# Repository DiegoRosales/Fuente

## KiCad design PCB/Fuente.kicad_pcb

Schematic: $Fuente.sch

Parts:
C1: 0.33uF
C2, C3, C5, C6: 0.1uF
C4, C7: 470uF
D1, D2, D3, D4, D9, D10, D11, D12, D17, D18, D19, D20, D25, D26, D27, D28: LED
D5, D6, D7, D8, D13, D14, D15, D16, D21, D22, D23, D24, D29, D30, D31, D32, D33: DIODE
FB1: FILTER
JP1: JUMPER
JP2: JUMPER
JP3: JUMPER3
MCU1: PRO_MINI_2
P1, P2, P3, P4, P5, P6, P7, P8, P9, P10, P11, P12, P13, P14, P15, P16, P17, P18: CONN_2
P19, P20: CONN_4
Q1, Q2, Q3, Q4, Q5, Q6, Q7, Q8, Q9, Q10, Q11, Q12, Q13, Q14, Q15, Q16: MOSFET_N
R1, R2, R3, R4, R5, R6, R7, R8, R9, R10, R11, R12, R13, R14, R15, R16, R17, R18, R19: 1k
SD1: MICROSD_MODULE
SW1, SW2, SW3, SW4, SW5, SW6, SW7, SW8, SW9, SW10, SW11, SW12, SW13, SW14, SW15, SW16: PUSHBUTTON
U1: 7805
U2, U3: 74HC595
U4: BTM_2

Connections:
1: SW1.2, U2.15 (QA)
2: SW5.2, U2.1 (QB)
3: SW9.2, U2.2 (QC)
4: SW13.2, U2.3 (QD)
5: SW2.2, U2.4 (QE)
6: SW6.2, U2.5 (QF)
7: SW10.2, U2.6 (QG)
8: SW14.2, U2.7 (QH)
9: SW3.2, U3.15 (QA)
10: SW7.2, U3.1 (QB)
11: SW11.2, U3.2 (QC)
12: SW15.2, U3.3 (QD)
13: SW4.2, U3.4 (QE)
14: SW8.2, U3.5 (QF)
15: SW12.2, U3.6 (QG)
16: SW16.2, U3.7 (QH)
+5V: C2.1, C3.1, C4.1, FB1.1, JP1.1, MCU1.25, SD1.3 (VCC), SW1.3, SW1.4, SW2.3, SW2.4, SW3.3, SW3.4, SW4.3, SW4.4, SW5.3, SW5.4, SW6.3, SW6.4, SW7.3, SW7.4, SW8.3, SW8.4, SW9.3, SW9.4, SW10.3, SW10.4, SW11.3, SW11.4, SW12.3, SW12.4, SW13.3, SW13.4, SW14.3, SW14.4, SW15.3, SW15.4, SW16.3, SW16.4, U2.10 (SRCLR), U2.16 (VCC), U3.10 (SRCLR), U3.16 (VCC)
+12P: C1.1, D33.2 (K), P18.2 (PM), U1.VI, U1.Vi
+12V: C5.1, C7.1, D5.2 (K), D6.2 (K), D7.2 (K), D8.2 (K), D13.2 (K), D14.2 (K), D15.2 (K), D16.2 (K), D21.2 (K), D22.2 (K), D23.2 (K), D24.2 (K), D29.2 (K), D30.2 (K), D31.2 (K), D32.2 (K), P1.1, P2.1, P3.1, P4.1, P5.1, P6.1, P7.1, P8.1, P9.1, P10.1, P11.1, P12.1, P13.1, P14.1, P15.1, P16.1, P17.2 (PM)
/M_S: JP2.1, MCU1.8
A0 (RX): MCU1.21, U4.3 (TX)
A1 (TX): MCU1.22, R18.2, R19.1
GND: C1.2, C2.2, C3.2, C4.2, C5.2, C6.2, C7.2, D1.2 (K), D2.2 (K), D3.2 (K), D4.2 (K), D9.2 (K), D10.2 (K), D11.2 (K), D12.2 (K), D17.2 (K), D18.2 (K), D19.2 (K), D20.2 (K), D25.2 (K), D26.2 (K), D27.2 (K), D28.2 (K), JP2.2, MCU1.4, MCU1.27, P17.1, P18.1, Q1.S, Q2.S, Q3.S, Q4.S, Q5.S, Q6.S, Q7.S, Q8.S, Q9.S, Q10.S, Q11.S, Q12.S, Q13.S, Q14.S, Q15.S, Q16.S, R17.1, SD1.2 (GND), U1.GND, U2.8 (GND), U3.8 (GND), U4.4 (GND)
unnamed: Q13.G, R13.2, SW13.1
unnamed: D25.1 (A), R13.1
unnamed: Q2.G, R2.2, SW2.1
unnamed: D17.1 (A), R9.1
unnamed: D9.1 (A), R5.1
unnamed: Q5.G, R5.2, SW5.1
unnamed: Q9.G, R9.2, SW9.1
unnamed: D18.1 (A), R10.1
unnamed: Q10.G, R10.2, SW10.1
unnamed: D26.1 (A), R14.1
unnamed: Q14.G, R14.2, SW14.1
unnamed: Q6.G, R6.2, SW6.1
unnamed: D2.1 (A), R2.1
unnamed: D10.1 (A), R6.1
unnamed: C6.1, D33.1 (A), JP1.2 (PM), U1.VO, U1.Vo
unnamed: JP3.2, U2.14 (SER)
unnamed: U2.9 (~QH), U3.14 (SER)
unnamed: FB1.2, U4.5 (Vcc)
unnamed: R17.2, R18.1, R19.2, U4.2 (RX)
unnamed: D1.1 (A), R1.1
unnamed: Q1.G, R1.2, SW1.1
unnamed: D19.1 (A), R11.1
unnamed: Q11.G, R11.2, SW11.1
unnamed: Q15.G, R15.2, SW15.1
unnamed: D27.1 (A), R15.1
unnamed: D3.1 (A), R3.1
unnamed: Q3.G, R3.2, SW3.1
unnamed: D11.1 (A), R7.1
unnamed: Q7.G, R7.2, SW7.1
unnamed: D20.1 (A), R12.1
unnamed: Q12.G, R12.2, SW12.1
unnamed: D28.1 (A), R16.1
unnamed: Q16.G, R16.2, SW16.1
unnamed: Q4.G, R4.2, SW4.1
unnamed: D4.1 (A), R4.1
unnamed: D12.1 (A), R8.1
unnamed: Q8.G, R8.2, SW8.1
OUT_1: D5.1 (A), P1.2 (PM), Q1.D
OUT_2: D13.1 (A), P2.2 (PM), Q5.D
OUT_3: D21.1 (A), P3.2 (PM), Q9.D
OUT_4: D29.1 (A), P4.2 (PM), Q13.D
OUT_5: D6.1 (A), P5.2 (PM), Q2.D
OUT_6: D14.1 (A), P6.2 (PM), Q6.D
OUT_7: D22.1 (A), P7.2 (PM), Q10.D
OUT_8: D30.1 (A), P8.2 (PM), Q14.D
OUT_9: D7.1 (A), P9.2 (PM), Q3.D
OUT_10: D15.1 (A), P10.2 (PM), Q7.D
OUT_11: D23.1 (A), P11.2 (PM), Q11.D
OUT_12: D31.1 (A), P12.2 (PM), Q15.D
OUT_13: D8.1 (A), P13.2 (PM), Q4.D
OUT_14: D16.1 (A), P14.2 (PM), Q8.D
OUT_15: D24.1 (A), P15.2 (PM), Q12.D
OUT_16: D32.1 (A), P16.2 (PM), Q16.D
SPI_CS: MCU1.17, SD1.7 (CS)
SPI_MISO: MCU1.19, SD1.4 (MISO)
SPI_MOSI: MCU1.18, SD1.5 (MOSI)
SPI_SCK: MCU1.20, SD1.6 (SCK)
SR_CLK: MCU1.12, P19.2, P20.2, U2.11 (SRCLK), U3.11 (SRCLK)
SR_Input: JP3.1, MCU1.9
SR_Input_conn: JP3.3, P19.1
SR_LCLK: MCU1.11, P19.4, P20.4, U2.12 (RCLK), U3.12 (RCLK)
SR_OE: MCU1.10, P19.3, P20.3, U2.13 (G), U3.13 (G)
SR_OUTPUT: P20.1, U3.9 (~QH)

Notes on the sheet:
Arduino - TX BTM - RX
Arduino - RX BTM - TX
Bluetooth Module
5V Regulator
Decoupling
LED PSU
Shift register
Digital PSU
Power Transistors
Connectors
Arduino and I2C

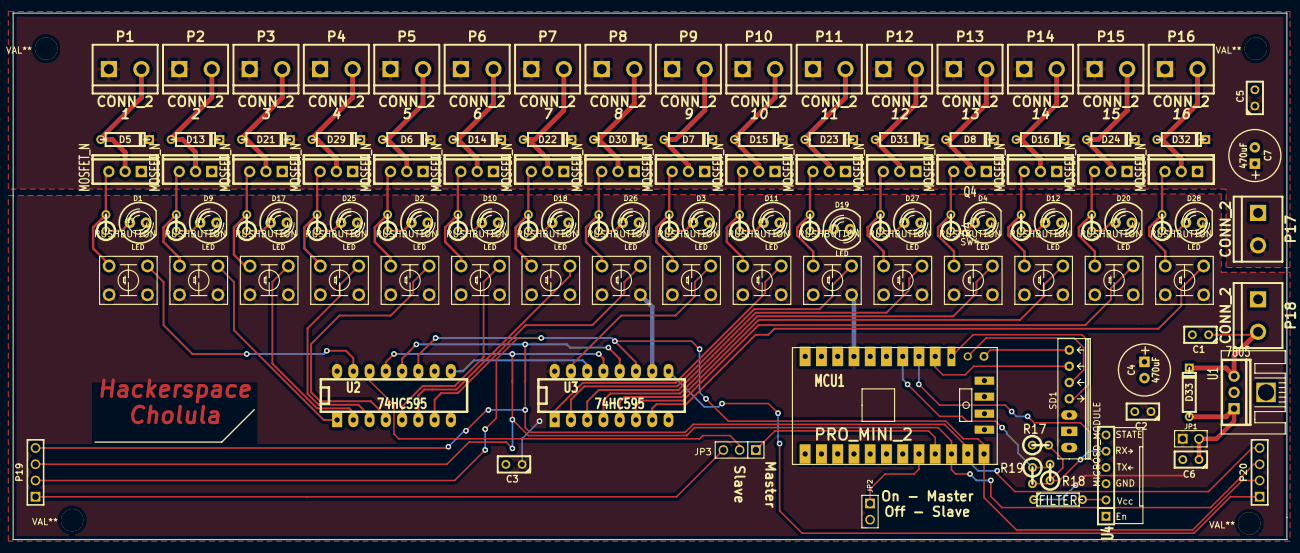
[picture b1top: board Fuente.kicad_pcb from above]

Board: 2 copper layers, 199.0 x 82.2 mm, 125 parts (0 on the bottom side), 86 nets.

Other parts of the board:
3.5mm_Screw, 3.5mm_Screw#2, 3.5mm_Screw#3, 3.5mm_Screw#4: VAL**; 3.5mm_Screw

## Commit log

2015-05-08 :tada: Added .gitattributes & .gitignore files
2015-05-08 Creacion
2015-05-08 Guarder
